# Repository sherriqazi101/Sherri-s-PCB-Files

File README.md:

# Sherri-s-PCB-Files
This file contains the PCB design for an arduino and includes the schematic.

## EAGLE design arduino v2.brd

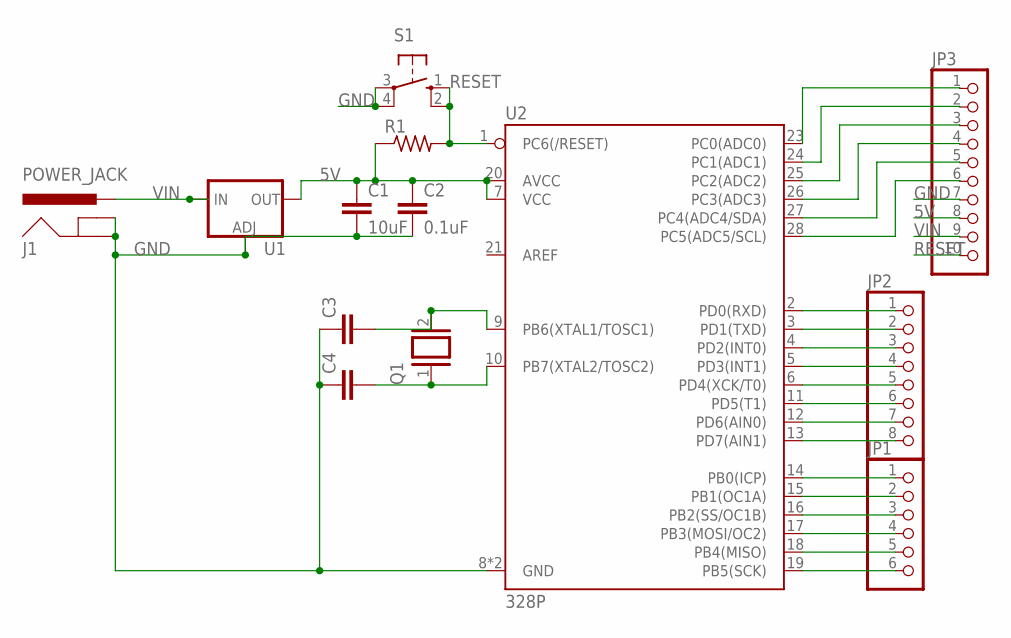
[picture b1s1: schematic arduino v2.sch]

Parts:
C1: 10uF; C025-024X044
C2: 0.1uF; C025-024X044
C3, C4: C-EU025-024X044; C025-024X044
J1: POWER_JACK; POWER_JACK_PTH
JP1: PINHD-1X6; 1X06
JP2: PINHD-1X8; 1X08
JP3: PINHD-1X10; 1X10
Q1: XTAL/S; QS
R1: R-US_0204/7; 0204/7
S1: 10-XX; B3F-10XX
U1: V_REG_LM1117SOT223; SOT223
U2: 328P; DIP28

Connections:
5V: C1.1, C2.1, JP3.8, R1.1, U1.2 (OUT), U1.4 (OUT), U2.7 (VCC), U2.20 (AVCC)
GND: C1.2, C2.2, C3.1, C4.1, J1.GND, J1.GNDBREAK, JP3.7, S1.3, S1.4 (P1), U1.1 (ADJ), U2.8 (GND), U2.22 (GND)
unnamed: JP1.1, U2.14 (PB0(ICP))
unnamed: C3.2, Q1.2, U2.9 (PB6(XTAL1/TOSC1))
unnamed: C4.2, Q1.1, U2.10 (PB7(XTAL2/TOSC2))
unnamed: JP1.2, U2.15 (PB1(OC1A))
unnamed: JP1.3, U2.16 (PB2(SS/OC1B))
unnamed: JP1.4, U2.17 (PB3(MOSI/OC2))
unnamed: JP1.5, U2.18 (PB4(MISO))
unnamed: JP1.6, U2.19 (PB5(SCK))
unnamed: JP2.1, U2.2 (PD0(RXD))
unnamed: JP2.2, U2.3 (PD1(TXD))
unnamed: JP2.3, U2.4 (PD2(INT0))
unnamed: JP2.4, U2.5 (PD3(INT1))
unnamed: JP2.5, U2.6 (PD4(XCK/T0))
unnamed: JP2.6, U2.11 (PD5(T1))
unnamed: JP2.7, U2.12 (PD6(AIN0))
unnamed: JP2.8, U2.13 (PD7(AIN1))
unnamed: JP3.1, U2.23 (PC0(ADC0))
unnamed: JP3.2, U2.24 (PC1(ADC1))
unnamed: JP3.3, U2.25 (PC2(ADC2))
unnamed: JP3.4, U2.26 (PC3(ADC3))
unnamed: JP3.5, U2.27 (PC4(ADC4/SDA))
unnamed: JP3.6, U2.28 (PC5(ADC5/SCL))
RESET: JP3.10, R1.2, S1.1 (S), S1.2 (S1), U2.1 (PC6(/RESET))
VIN: J1.PWR, JP3.9, U1.3 (IN)

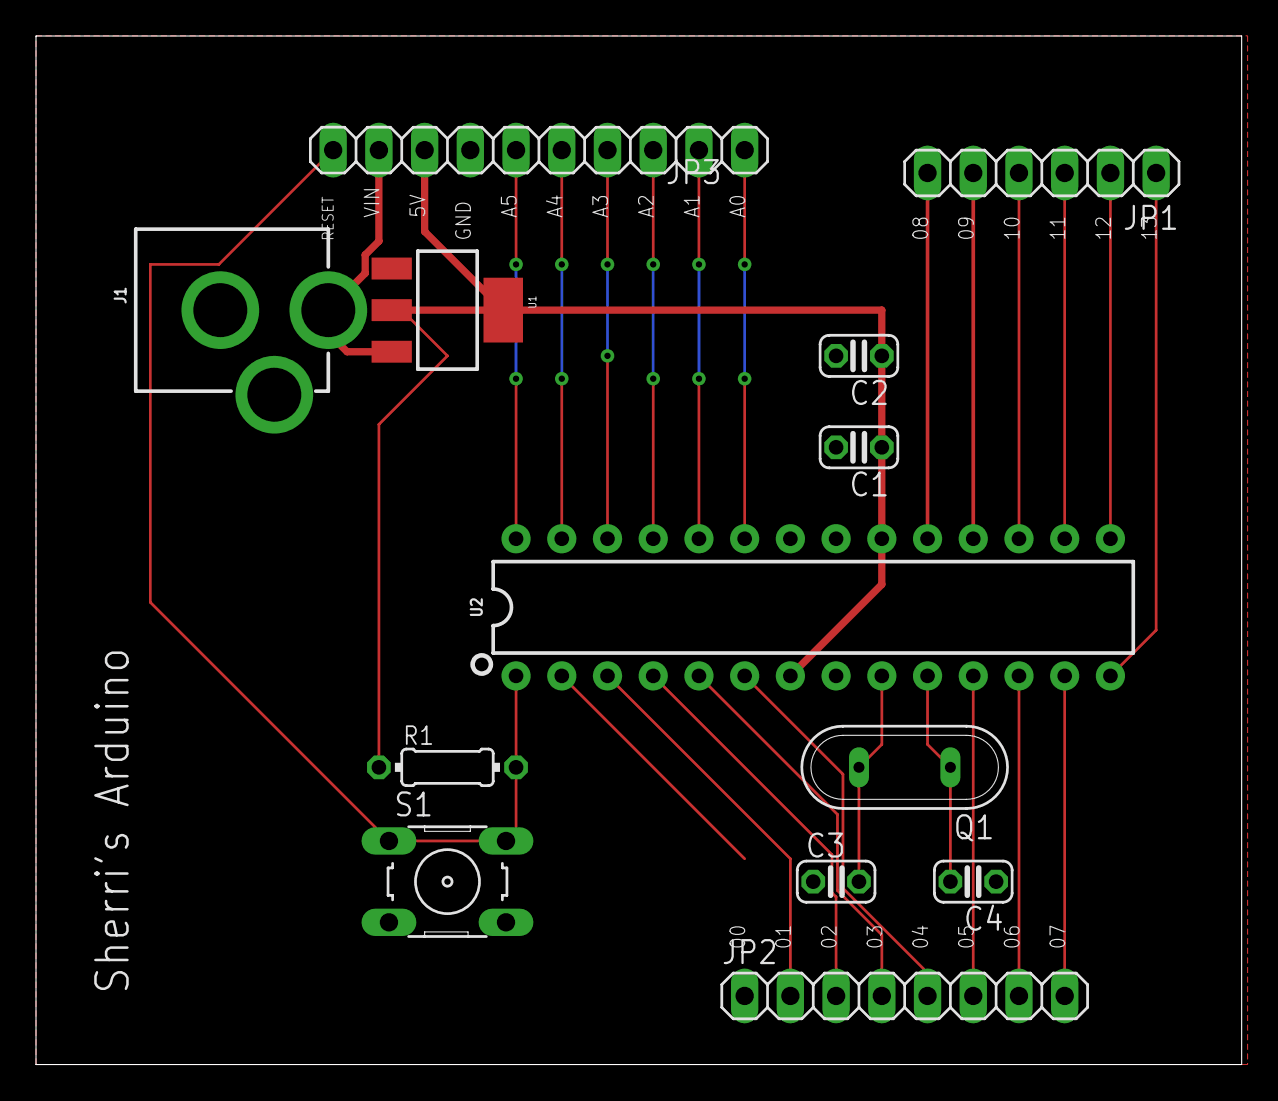
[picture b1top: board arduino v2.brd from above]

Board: 2 copper layers, 67.0 x 57.1 mm, 13 parts (0 on the bottom side), 26 nets.

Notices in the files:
parts and their libraries:
SparkFun-Connectors: Licensing: Creative Commons ShareAlike 4.0 International - https://creativecommons.org/licenses/by-sa/4.0
